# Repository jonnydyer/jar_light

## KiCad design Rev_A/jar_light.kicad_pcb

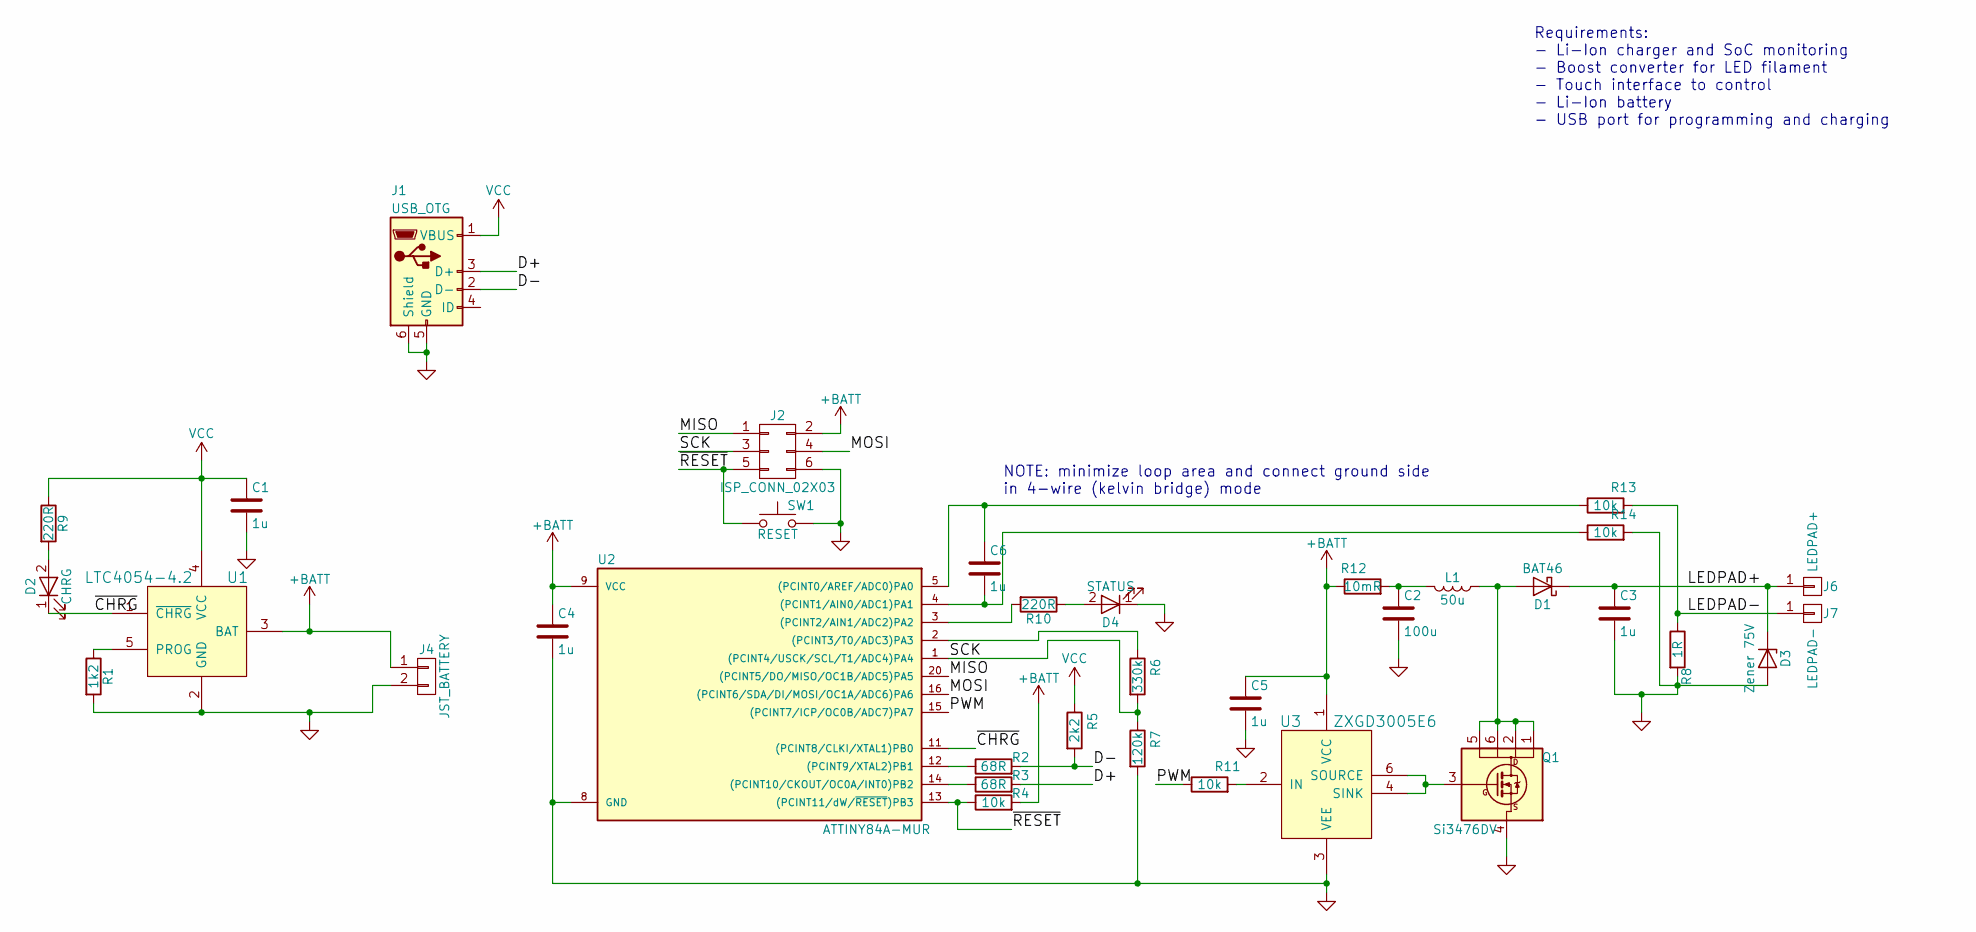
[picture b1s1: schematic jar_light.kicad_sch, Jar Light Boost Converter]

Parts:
C1, C4, C5, C6: 1u; C_0603
C2: 100u; C_1206
C3: 1u; C_1206
D1: BAT46; D_SOD-123
D2: CHRG; LED_0603
D3: Zener 75V; D_SOD-123
D4: STATUS; LED_0603
J1: USB_OTG; USB_Mirco-B_Molex-105017-0001
J2: ISP_CONN_02X03; Pin_Header_Straight_2x03_Pitch2.54mm
J4: JST_BATTERY; s2b-ph-sm4-tb_w3d
J6: LEDPAD+; Measurement_Point_Square-TH_Big
J7: LEDPAD-; Measurement_Point_Square-TH_Big
L1: 50u; L_6.3x6.3_H3
Q1: Si3476DV; TSOP-6
R1: 1k2; R_0603
R2, R3: 68R; R_0603
R4, R11, R13, R14: 10k; R_0603
R5: 2k2; R_0603
R6: 330k; R_0603
R7: 120k; R_0603
R8: 1R; R_0603
R9, R10: 220R; R_0603
R12: 10mR; R_0603
SW1: RESET; SW_SPST_KMR2
U1: LTC4054-4.2; TSOT-23-5
U2: ATTINY84A-MUR; QFN-20-1EP_4x4mm_Pitch0.5mm
U3: ZXGD3005E6; SOT-23-6

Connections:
+BATT: C4.1, C5.1, J2.2, J4.1, R4.2, R12.1, U1.3 (BAT), U2.9 (VCC), U3.1 (VCC)
/D+: J1.3 (D+), R3.2
/D-: J1.2 (D-), R2.2, R5.2
/LEDPAD+: C3.1, D1.1 (K), D3.1 (K), J6.1
/LEDPAD-: J7.1, R8.1, R13.2
/MISO: J2.1, U2.20 ((PCINT5/DO/MISO/OC1B/ADC5)PA5)
/MOSI: J2.4, U2.16 ((PCINT6/SDA/DI/MOSI/OC1A/ADC6)PA6)
/PWM: R11.1, U2.15 ((PCINT7/ICP/OC0B/ADC7)PA7)
/SCK: J2.3, R6.2, R7.1, U2.1 ((PCINT4/USCK/SCL/T1/ADC4)PA4)
/~CHRG: D2.1 (K), U1.1 (~CHRG), U2.11 ((PCINT8/CLKI/XTAL1)PB0)
/~RESET: J2.5, R4.1, SW1.1, U2.13 ((PCINT11/dW/~RESET)PB3)
GND: C1.2, C2.2, C3.2, C4.2, C5.2, D3.2 (A), D4.1 (K), J1.5 (GND), J1.6 (Shield), J2.6, J4.2, Q1.4 (G), R1.2, R7.2, R8.2, R14.2, SW1.2, U1.2 (GND), U2.8 (GND), U2.21, U3.3 (VEE)
unnamed: C2.1, L1.2, R12.2
unnamed: C6.1, R13.1, U2.5 ((PCINT0/AREF/ADC0)PA0)
unnamed: C6.2, R14.1, U2.4 ((PCINT1/AIN0/ADC1)PA1)
unnamed: D1.2 (A), L1.1, Q1.1 (S), Q1.2 (S), Q1.5 (D), Q1.6 (D)
unnamed: D2.2 (A), R9.2
unnamed: D4.2 (A), R10.1
unnamed: Q1.3 (S), U3.4 (SINK), U3.6 (SOURCE)
unnamed: R1.1, U1.5 (PROG)
unnamed: R2.1, U2.12 ((PCINT9/XTAL2)PB1)
unnamed: R3.1, U2.14 ((PCINT10/CKOUT/OC0A/INT0)PB2)
unnamed: R6.1, U2.2 ((PCINT3/T0/ADC3)PA3)
unnamed: R10.2, U2.3 ((PCINT2/AIN1/ADC2)PA2)
unnamed: R11.2, U3.2 (IN)
VCC: C1.1, J1.1 (VBUS), R5.1, R9.1, U1.4 (VCC)

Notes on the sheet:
NOTE: minimize loop area and connect ground side in 4-wire (kelvin bridge) mode
Requirements: - Li-Ion charger and SoC monitoring - Boost converter for LED filament - Touch interface to control - Li-Ion battery - USB port for programming and charging

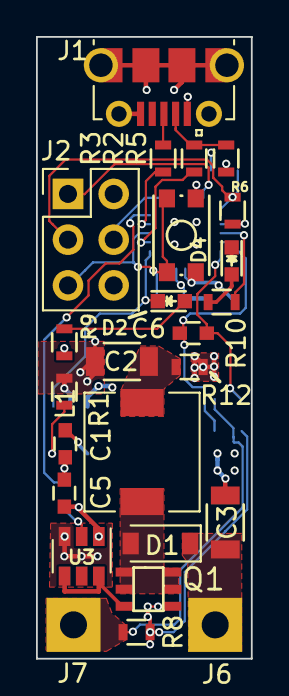
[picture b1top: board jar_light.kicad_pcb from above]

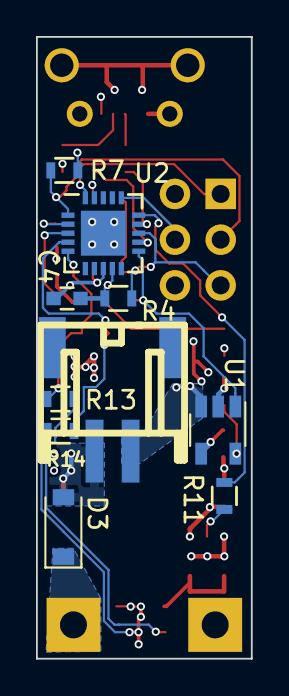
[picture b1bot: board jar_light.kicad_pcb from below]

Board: 4 copper layers, 11.9 x 34.5 mm, 35 parts (10 on the bottom side), 26 nets.

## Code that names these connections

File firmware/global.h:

//
#ifndef GLOBAL_H
#define GLOBAL_H

// global AVRLIB defines
#include "avrlibdefs.h"
// global AVRLIB types definitions
#include "avrlibtypes.h"

#define SYSTICK_RATE 50
#define BTN_HOLD_TIME 3
#define TELEM_SLOW_DELAY 1.0
#define LED_UPDATE_DELAY 10
#define LED_FLASH_TICKS 17
// Debug defines
// MUST SUM TO 32!!
#define EEPR_MAX_ENTRIES 128      // 512/4
//#define EEPR_SAVE_ENABLE 1
//#define SPI_TLM_OUTPUT 1
//#define RAMP_PWM_MODE 1


#if defined(REV_A) || defined(REV_B)
// Defines

#define PWM_MASK (1<<PA7)

// Macros
#define TOGGLE_LED(x) PORTA = (PORTA & ~(x)) | (PORTA ^ (x))

#endif

#if defined(REV_A)
#define LED_MASK (1<<PA2)
#define ENABLE_BATT_MEAS DDRA |= (1<<PA3); PORTA |= (1<<PA3)
#define DISABLE_BATT_MEAS //DDRA &= ~(1<<PA3); PORTA &= ~(1<<PA3)

// BTN is not connected to PA4 on REV_A, but we have it hear so that it compiles.
// If BTN is needed, it can be accessed as the SCK line on the ISP header
#define BTN_MASK (1<<PA4)

// 20x differential input with ADC1(PA1) negative, ADC3 (PA3) positive; 1.1V ref
#define ADMUX_CURR (1<<MUX0) | (1<<MUX1) | (1<<MUX2) | (1<<MUX3) | (1<<MUX5) | (1<<REFS1)
#define ADMUX_VOLT (1<<MUX0) | (1<<MUX5)        // Internal reference
#define ADMUX_TEMP (1<<MUX1) | (1<<MUX5) | (1<<REFS1)

#elif defined(REV_B)
#define LED_MASK (1<<PA3)
#define BTN_MASK (1<<PA4)

#define ENABLE_BATT_MEAS 
#define DISABLE_BATT_MEAS 
// 20x differential input with ADC2(PA2) negative, ADC1 (PA1) positive; 1.1V ref
#define ADMUX_CURR (1<<MUX0) | (1<<MUX2) | (1<<MUX3) | (1<<REFS1)
#define ADMUX_VOLT (1<<MUX0) | (1<<MUX5)        // Internal reference
#define ADMUX_TEMP (1<<MUX1) | (1<<MUX5) | (1<<REFS1)

#else
#error "BOARD_REV must be one of [REV_A]"

#endif

#endif

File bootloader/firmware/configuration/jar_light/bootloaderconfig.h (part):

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 * 
 * Controller type: ATtiny 84 - 12 MHz
 * Configuration:   Default configuration
 *       USB D- :   PB1
 *       USB D+ :   PB2
 *       Entry  :   Always
 *       LED    :   PA2, Active High
 *       OSCCAL :   Save OSCAL and load for user program (12 MHz)
 * Note: can use 12 MHz V-USB without PLL due to stable RC-osc in ATTiny84A
 * Last Change:     Mar 16,2014
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 *                      external jumper. 
 *                      Adds 34 bytes.
 *
 *       JUMPER_PIN     Pin the jumper is connected to. (e.g. PB0)
 *       JUMPER_PORT    Port out register for the jumper (e.g. PORTB)  
 *       JUMPER_DDR     Port data direction register for the jumper (e.g. DDRB)  
 *       JUMPER_INP     Port inout register for the jumper (e.g. PINB)  
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
#define ENTRYMODE ENTRY_EXT_OR_WD

#define JUMPER_PIN    PB0
#define JUMPER_PORT   PORTB 
#define JUMPER_DDR    DDRB 
#define JUMPER_INP    PINB 
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#define LED_DDR     DDRA
#define LED_PORT    PORTA
#if defined(REV_A)
#define LED_PIN     PA2
#elif defined(REV_B)
#define LED_PIN     PA3
#else
#error "BOARD_REV must be one of REV_A, REV_B"
#endif
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
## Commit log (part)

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2019-06-29 Divided old kicad repo into separate repos per-project
2020-08-23 added gitignore
2020-08-23 Added backups
2020-08-23 added cache and rescue file for 4.x to 5.x convert
2020-08-23 fixed gitignore

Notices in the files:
bootloader/firmware/configuration/jar_light/bootloaderconfig.h:
License: GNU GPL v2 (see License.txt
